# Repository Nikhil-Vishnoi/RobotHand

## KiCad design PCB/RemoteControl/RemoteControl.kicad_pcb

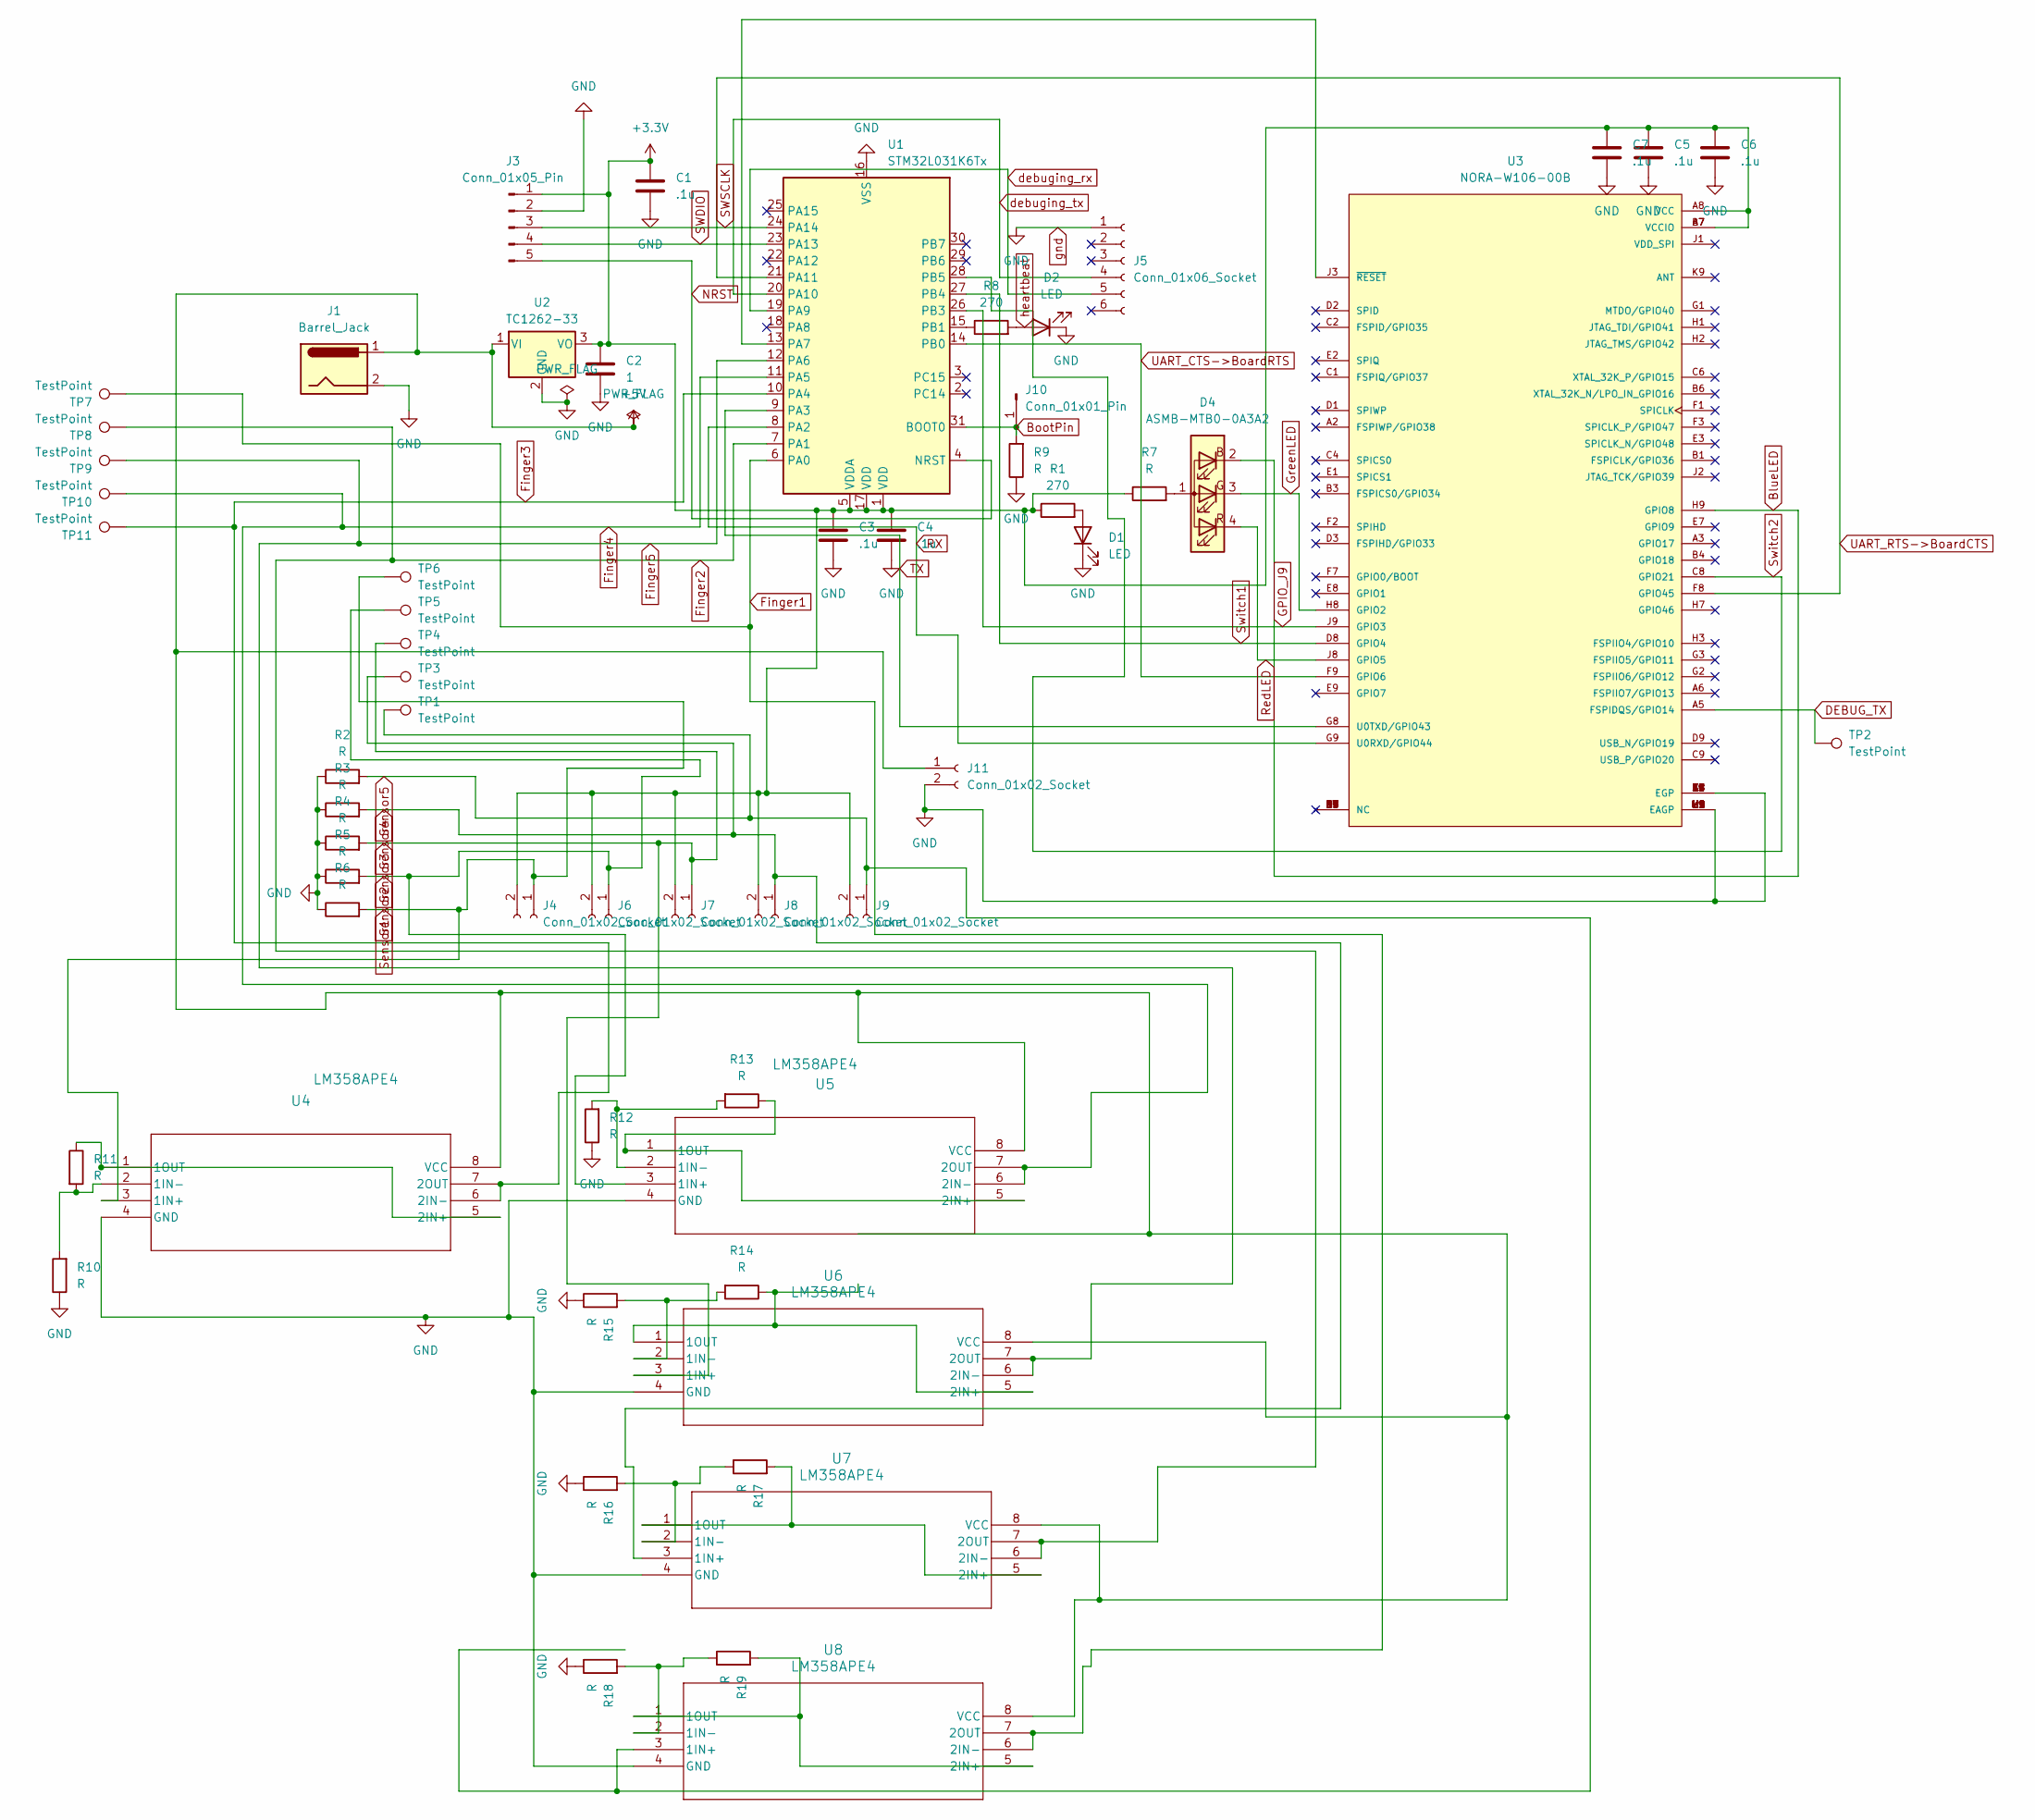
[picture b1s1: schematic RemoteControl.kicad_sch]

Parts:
C1, C3, C4, C5, C6, C7: .1u; C_0805_2012Metric_Pad1.18x1.45mm_HandSolder
C2: 1; C_0805_2012Metric_Pad1.18x1.45mm_HandSolder
D1, D2: LED; LED_1206_3216Metric_Pad1.42x1.75mm_HandSolder
D4: ASMB-MTB0-0A3A2; LED_Avago_PLCC4_3.2x2.8mm_CW
J1: Barrel_Jack; BarrelJack_Wuerth_694106106102_2.0x5.5mm
J3: Conn_01x05_Pin; PinHeader_1x05_P2.54mm_Vertical
J4, J6, J7, J8, J9, J11: Conn_01x02_Socket; PinSocket_1x02_P2.54mm_Horizontal
J5: Conn_01x06_Socket; PinHeader_1x06_P2.54mm_Vertical
J10: Conn_01x01_Pin; PinHeader_1x01_P2.54mm_Vertical
R1, R8: 270; R_0805_2012Metric_Pad1.20x1.40mm_HandSolder
R2, R3, R4, R5, R6, R7, R9, R10, R11, R12, R13, R14, R15, R16, R17, R18, R19: R; R_0805_2012Metric_Pad1.20x1.40mm_HandSolder
TP1, TP2, TP3, TP4, TP5, TP6, TP7, TP8, TP9, TP10, TP11: TestPoint; TestPoint_Pad_2.5x2.5mm
U1: STM32L031K6Tx; LQFP-32_7x7mm_P0.8mm
U2: TC1262-33; SOT-223-3_TabPin2
U3: NORA-W106-00B; XCVR_NORA-W106-00B; PARTREV R03
U4, U5, U6, U7, U8: LM358APE4; P8

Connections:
+3.3V: C1.1, C2.1, C3.1, C4.1, C5.1, C6.1, C7.1, J3.1, J4.2, J6.2, J7.2, J8.2, J9.2, R1.1, R7.1, U1.1 (VDD), U1.5 (VDDA), U1.17 (VDD), U2.3 (VO), U3.A7 (VCCIO), U3.A8 (VCC), U3.B7 (VCCIO)
+5V: J1.1, J11.1, U2.1 (VI), U4.8 (VCC), U5.8 (VCC), U6.8 (VCC), U7.8 (VCC), U8.8 (VCC)
BlueLED: D4.2 (BK), U3.H9 (GPIO8)
BootPin: J10.1, R9.2, U1.31 (BOOT0)
DEBUG_TX: TP2.1, U3.A5 (FSPIDQS/GPIO14)
Finger1: TP7.1, U1.6 (PA0), U8.6 (2IN-), U8.7 (2OUT)
Finger2: TP8.1, U1.7 (PA1), U7.6 (2IN-), U7.7 (2OUT)
Finger3: TP11.1, U1.10 (PA4), U4.6 (2IN-), U4.7 (2OUT)
Finger4: TP10.1, U1.11 (PA5), U5.6 (2IN-), U5.7 (2OUT)
Finger5: TP9.1, U1.12 (PA6), U6.6 (2IN-), U6.7 (2OUT)
GPIO_J9: U1.26 (PB3), U3.J9 (GPIO3)
GreenLED: D4.3 (GK), U3.H8 (GPIO2)
NRST: J3.5, U1.4 (NRST)
unnamed: D1.2 (A), R1.2
unnamed: D2.2 (A), R8.2
unnamed: D4.1 (A), R7.2
unnamed: U1.13 (PA7), U3.J3 (~RESET)
unnamed: R8.1, U1.15 (PB1)
unnamed: R10.2, R11.2, U4.2 (1IN-)
unnamed: R11.1, U4.1 (1OUT), U4.5 (2IN+)
unnamed: R12.2, R13.2, U5.2 (1IN-)
unnamed: R13.1, U5.1 (1OUT), U5.5 (2IN+)
unnamed: R14.2, R15.2, U6.2 (1IN-)
unnamed: R14.1, U6.1 (1OUT), U6.5 (2IN+)
unnamed: R16.2, R17.1, U7.2 (1IN-)
unnamed: R17.2, U7.1 (1OUT), U7.5 (2IN+)
unnamed: R18.2, R19.1, U8.2 (1IN-)
unnamed: R19.2, U8.1 (1OUT), U8.5 (2IN+)
RX: U1.8 (PA2), U3.G9 (U0RXD/GPIO44)
RedLED: D4.4 (RK), U3.J8 (GPIO5)
SWDIO: J3.4, U1.23 (PA13)
SWSCLK: J3.3, U1.24 (PA14)
Sensor1: J4.1, R6.2, TP6.1, U4.3 (1IN+)
Sensor2: J6.1, R5.2, TP5.1, U5.3 (1IN+)
Sensor3: J7.1, R4.2, TP4.1, U6.3 (1IN+)
Sensor4: J8.1, R3.2, TP3.1, U7.3 (1IN+)
Sensor5: J9.1, R2.2, TP1.1, U8.3 (1IN+)
Switch1: U1.27 (PB4), U3.D8 (GPIO4)
Switch2: U1.28 (PB5), U3.C8 (GPIO21)
TX: U1.9 (PA3), U3.G8 (U0TXD/GPIO43)
UART_CTS->BoardRTS: U1.14 (PB0), U3.F9 (GPIO6)
UART_RTS->BoardCTS: U1.21 (PA11), U3.F8 (GPIO45)
debuging_rx: J5.5, U1.19 (PA9)
debuging_tx: J5.4, U1.20 (PA10)
gnd: C1.2, C2.2, C3.2, C4.2, C5.2, C6.2, C7.2, D1.1 (K), D2.1 (K), J1.2, J3.2, J5.1, J11.2, R2.1, R3.1, R4.1, R5.1, R6.1, R9.1, R10.1, R12.1, R15.1, R16.1, R18.1, U1.16 (VSS), U1.32 (VSS), U2.2 (GND), U3.A1 (EGP), U3.A9 (EGP), U3.B2 (EGP), U3.B8 (EGP), U3.E4 (EGP), U3.E5 (EGP), U3.F4 (EGP), U3.F5 (EGP), U3.K2 (EGP), U3.K3 (EGP), U3.K5 (EGP), U3.K7 (EGP), U3.K8 (EGP), U3.L1 (EAGP), U3.L9 (EAGP), U3.M1 (EAGP), U3.M2 (EAGP), U3.M8 (EAGP), U3.M9 (EAGP), U4.4 (GND), U5.4 (GND), U6.4 (GND), U7.4 (GND), U8.4 (GND)

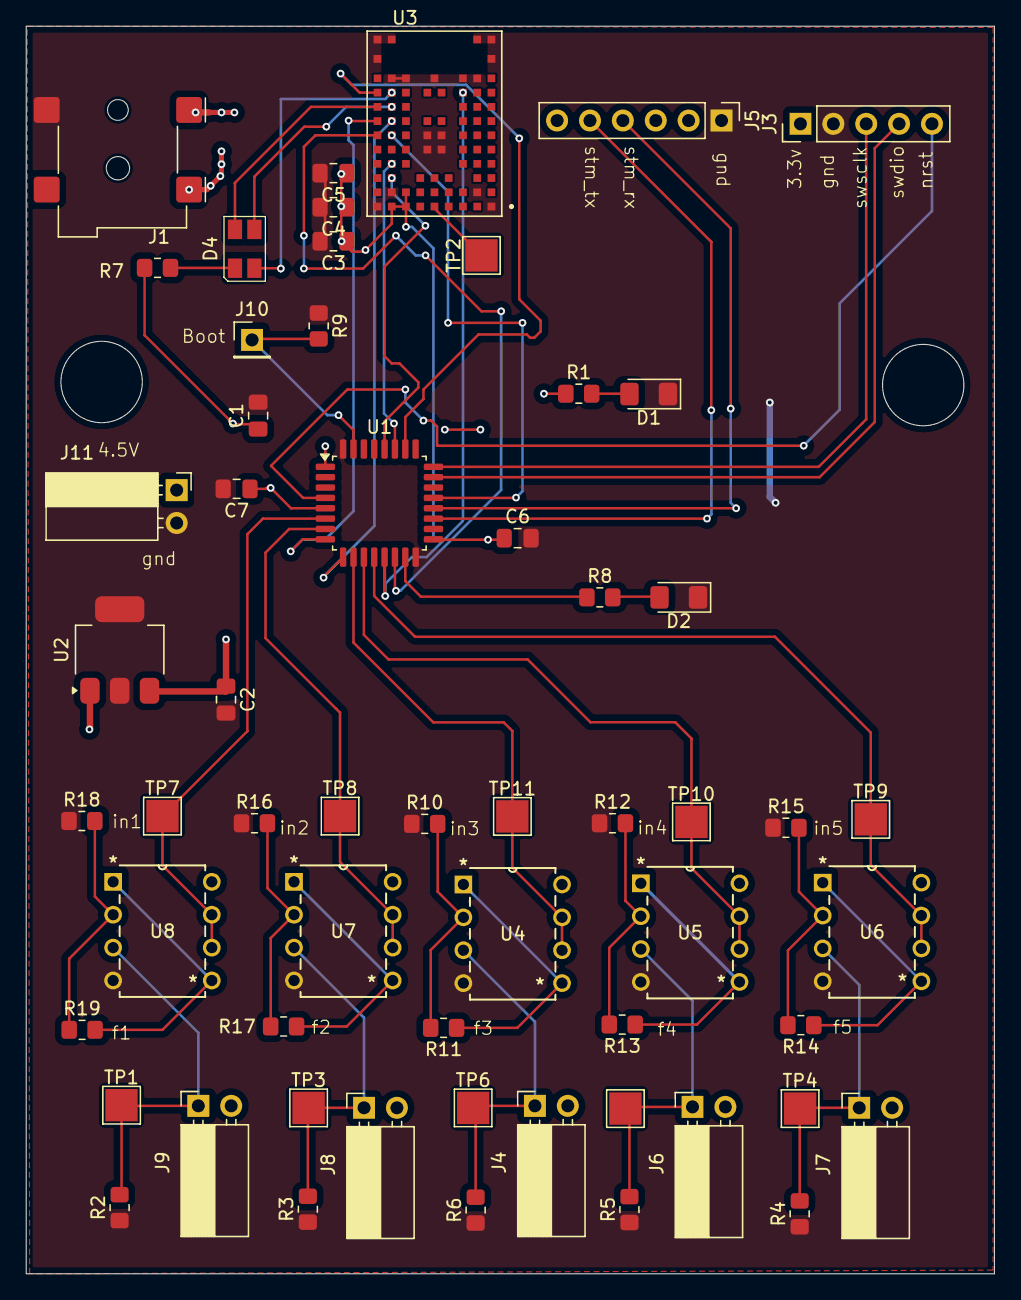
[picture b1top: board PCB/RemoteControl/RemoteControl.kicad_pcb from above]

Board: 2 copper layers, 74.8 x 96.4 mm, 58 parts (0 on the bottom side), 45 nets.

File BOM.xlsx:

Servo Controller
Reference | Qty | Value | DNP | Exclude from BOM | Exclude from Board | Footprint | Datasheet | Digikey Link
C1,C2,C5,C6,C7,C4 | 6.0 | .1u |  |  |  | Capacitor_SMD:C_0504_1310Metric_Pad0.83x1.28mm_HandSolder | ~ | https://www.digikey.com/en/products/detail/passive-plus/0505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
C3 | 1.0 | 1.0 |  |  |  | Capacitor_SMD:C_0504_1310Metric_Pad0.83x1.28mm_HandSolder | ~ | https://www.digikey.com/en/products/detail/murata-electronic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
D1 | 1.0 | ASMB-MTB0-0A3A2 |  |  |  | LED_SMD:LED_Avago_PLCC4_3.2x2.8mm_CW | https://docs.broadcom.com/docs/AV02-4186EN | https://www.mouser.com/ProductDetail/Broadcom-Avago/ASMB-MTB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
D2,D3 | 2.0 | LED |  |  |  | LED_SMD:LED_1206_3216Metric_Pad1.42x1.75mm_HandSolder | ~ | https://www.digikey.com/en/products/detail/everlight-electro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
J1,J2,J3,J4,J7 | 5.0 | Conn_01x03_Pin |  |  |  | Connector_PinHeader_2.54mm:PinHeader_1x03_P2.54mm_Horizontal | ~ | https://www.digikey.com/en/products/detail/w-rth-elektronik/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
J5 | 1.0 | Conn_01x05_Pin |  |  |  | Connector_PinHeader_2.54mm:PinHeader_1x05_P2.54mm_Vertical | ~ | https://www.digikey.com/en/products/detail/te-connectivity-a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
J6 | 1.0 | Conn_01x02_Socket |  |  |  | Connector_PinSocket_2.54mm:PinSocket_1x02_P2.54mm_Horizontal | ~ | https://www.digikey.com/en/products/detail/sullins-connector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
J8 | 1.0 | Barrel_Jack |  |  |  | Connector_BarrelJack:BarrelJack_Wuerth_694106106102_2.0x5.5mm | ~ | https://www.digikey.com/en/products/detail/w-rth-elektronik/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
J9 | 1.0 | Conn_01x06_Socket |  |  |  | Connector_PinSocket_2.54mm:PinSocket_1x06_P2.54mm_Vertical | ~ | https://www.digikey.com/en/products/detail/sullins-connector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
J10 | 1.0 | Conn_01x01_Pin |  |  |  | Connector_PinHeader_2.54mm:PinHeader_1x01_P2.54mm_Vertical | ~ | https://www.digikey.com/en/products/detail/te-connectivity-a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
R1,R3,R4,R2 | 4.0 | 270.0 |  |  |  | Resistor_SMD:R_0805_2012Metric_Pad1.20x1.40mm_HandSolder | ~ | https://www.digikey.com/en/products/detail/panasonic-electro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
TP1,TP2,TP3 | 3.0 | TestPoint |  |  |  | TestPoint:TestPoint_Pad_2.5x2.5mm | ~ | Already on Board
U1 | 1.0 | PCA9685PW |  |  |  | Package_SO:TSSOP-28_4.4x9.7mm_P0.65mm | http://www.nxp.com/docs/en/data-sheet/PCA9685.pdf | Have
U2 | 1.0 | NORA-W106-00B |  |  |  | NORA-W106-00B:XCVR_NORA-W106-00B |  | Have
U3 | 1.0 | TC1262-33 |  |  |  | Package_TO_SOT_SMD:SOT-223-3_TabPin2 | http://ww1.microchip.com/downloads/en/DeviceDoc/21373C.pdf | https://www.digikey.com/en/products/detail/microchip-technol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
U4 | 1.0 | STM32L031K6Tx |  |  |  | Package_QFP:LQFP-32_7x7mm_P0.8mm | https://www.st.com/resource/en/datasheet/stm32l031k6.pdf | Get from supply closet
Servo | 5.0 |  |  |  |  |  |  | https://www.digikey.com/en/products/detail/hitec-commercial-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
Remort Controller
Reference | Qty | Value | DNP | Exclude from BOM | Exclude from Board | Footprint | Datasheet | Digikey Buy Link
C1,C3,C4,C5,C6,C7 | 6.0 | .1u |  |  |  | Capacitor_SMD:C_0504_1310Metric_Pad0.83x1.28mm_HandSolder | ~ | https://www.mouser.com/ProductDetail/Samsung-Electro-Mechani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
C2 | 1.0 | 1.0 |  |  |  | Capacitor_SMD:C_0504_1310Metric_Pad0.83x1.28mm_HandSolder | ~ | https://www.digikey.com/en/products/detail/murata-electronic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
D1,D2 | 2.0 | LED |  |  |  | LED_SMD:LED_1206_3216Metric_Pad1.42x1.75mm_HandSolder | ~ | https://www.digikey.com/en/products/detail/everlight-electro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
D4 | 1.0 | ASMB-MTB0-0A3A2 |  |  |  | LED_SMD:LED_Avago_PLCC4_3.2x2.8mm_CW | https://docs.broadcom.com/docs/AV02-4186EN | https://www.mouser.com/ProductDetail/Broadcom-Avago/ASMB-MTB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
J1 | 1.0 | Barrel_Jack |  |  |  | Connector_BarrelJack:BarrelJack_Wuerth_694106106102_2.0x5.5mm | ~ | https://www.digikey.com/en/products/detail/w-rth-elektronik/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
J3 | 1.0 | Conn_01x05_Pin |  |  |  | Connector_PinHeader_2.54mm:PinHeader_1x05_P2.54mm_Vertical | ~ | https://www.digikey.com/en/products/detail/te-connectivity-a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
J4,J6,J7,J8,J9,J11 | 6.0 | Conn_01x02_Socket |  |  |  | Connector_PinSocket_2.54mm:PinSocket_1x02_P2.54mm_Horizontal | ~ | https://www.digikey.com/en/products/detail/sullins-connector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
J5 | 1.0 | Conn_01x06_Socket |  |  |  | Connector_PinHeader_2.54mm:PinHeader_1x06_P2.54mm_Vertical | ~ | https://www.digikey.com/en/products/detail/sullins-connector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
J10 | 1.0 | Conn_01x01_Pin |  |  |  | Connector_PinHeader_2.54mm:PinHeader_1x01_P2.54mm_Vertical | ~ | https://www.digikey.com/en/products/detail/te-connectivity-a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
R1,R8,R9,R7 | 2.0 | 270.0 |  |  |  | Resistor_SMD:R_0805_2012Metric_Pad1.20x1.40mm_HandSolder | ~ | https://www.digikey.com/en/products/detail/panasonic-electro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
R2,R3,R4,R5,R6 | 5.0 | 200k |  |  |  | Resistor_SMD:R_0805_2012Metric_Pad1.20x1.40mm_HandSolder | ~ | https://www.digikey.com/en/products/detail/yageo/RC0805JR-07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
R11,R13,R14,R17,R19 | 5.0 | 10k |  |  |  | Resistor_SMD:R_0805_2012Metric_Pad1.20x1.40mm_HandSolder | ~ | https://www.digikey.com/en/products/detail/yageo/RC0805FR-07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
R10,R12,R15,R16,R18 | 17.0 | 5k |  |  |  | Resistor_SMD:R_0805_2012Metric_Pad1.20x1.40mm_HandSolder | ~ | https://www.digikey.com/en/products/detail/vishay-dale/CRCW0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
TP1,TP2,TP3,TP4,TP5,TP6,TP7,TP8,TP9,TP10,TP11 | 11.0 | TestPoint |  |  |  | TestPoint:TestPoint_Pad_2.5x2.5mm | ~ | Already on Board
U1 | 1.0 | STM32L031K6Tx |  |  |  | Package_QFP:LQFP-32_7x7mm_P0.8mm | https://www.st.com/resource/en/datasheet/stm32l031k6.pdf | Get from the supply closet
U2 | 1.0 | TC1262-33 |  |  |  | Package_TO_SOT_SMD:SOT-223-3_TabPin2 | http://ww1.microchip.com/downloads/en/DeviceDoc/21373C.pdf | https://www.digikey.com/en/products/detail/microchip-technol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
U3 | 1.0 | NORA-W106-00B |  |  |  | NORA-W106-00B:XCVR_NORA-W106-00B |  | Have
U4,U5,U6,U7,U8 | 5.0 | LM358APE4 |  |  |  | lm358:P8 | https://www.ti.com/lit/gpn/lm358 | https://www.digikey.com/en/products/detail/texas-instruments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
 | 5.0

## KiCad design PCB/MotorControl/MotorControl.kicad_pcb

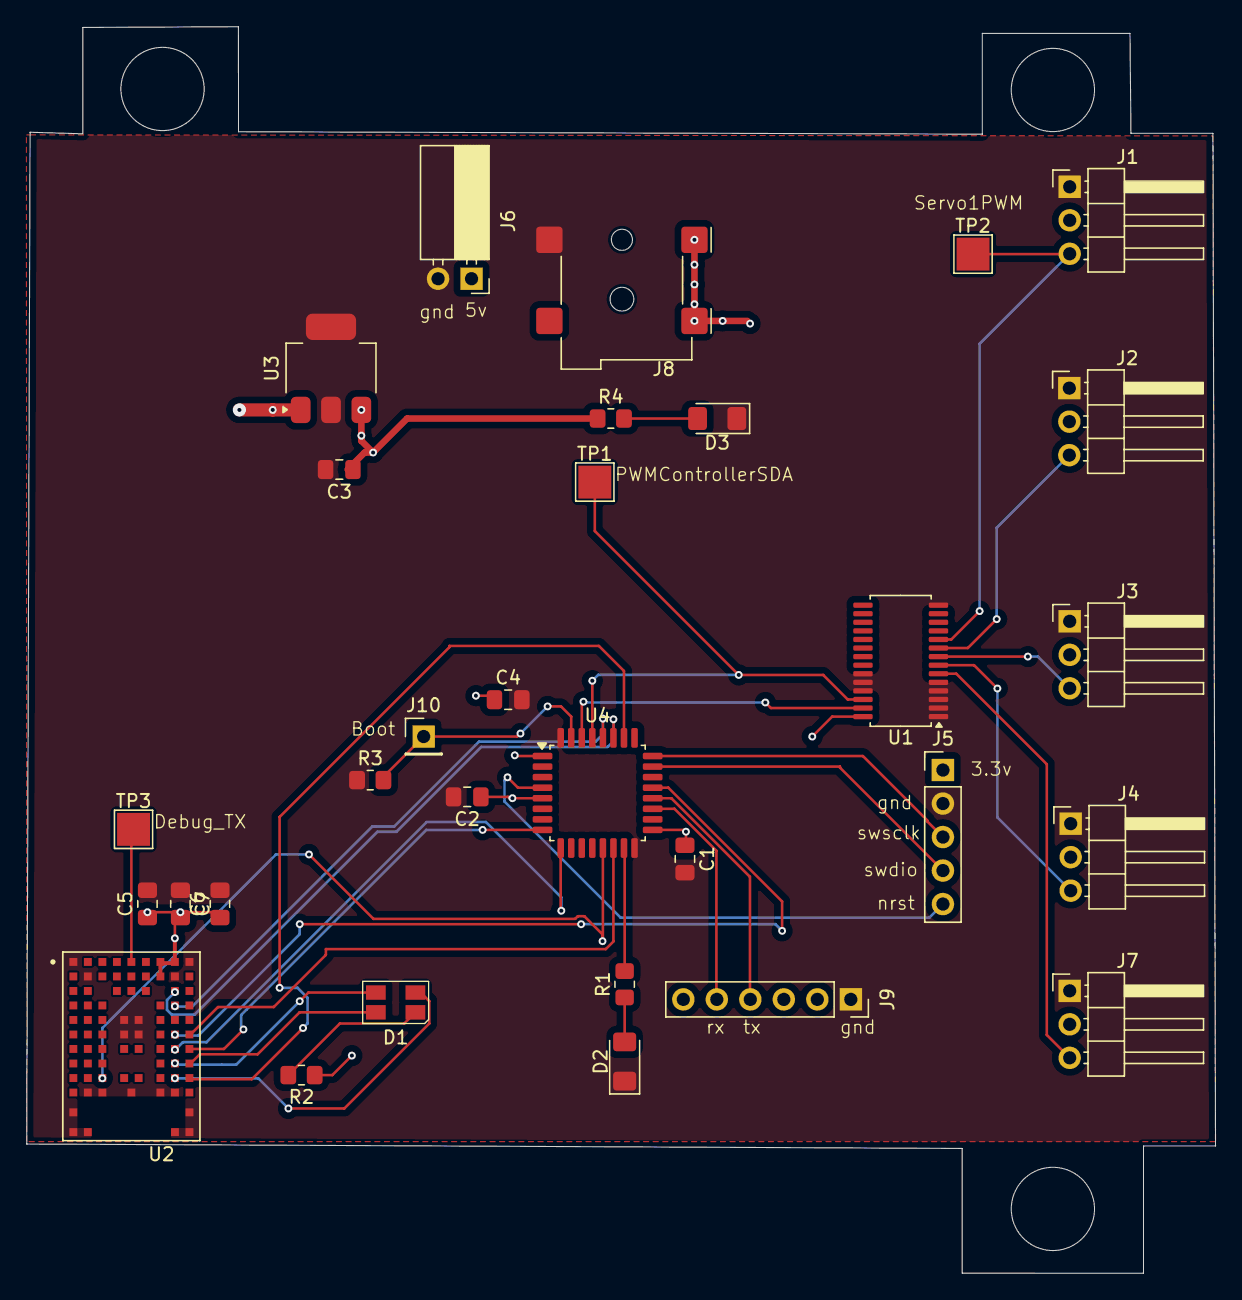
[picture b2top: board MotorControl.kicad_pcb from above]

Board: 2 copper layers, 90.1 x 94.5 mm, 31 parts (0 on the bottom side), 32 nets.

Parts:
C1, C2, C5, C6, C7: C; C_0805_2012Metric_Pad1.18x1.45mm_HandSolder
C3: 1; C_0805_2012Metric_Pad1.18x1.45mm_HandSolder
C4: .1u; C_0805_2012Metric_Pad1.18x1.45mm_HandSolder
D1: ASMB-MTB0-0A3A2; LED_Avago_PLCC4_3.2x2.8mm_CW
D2, D3: LED; LED_1206_3216Metric_Pad1.42x1.75mm_HandSolder
J1, J2, J3, J4, J7: Conn_01x03_Pin; PinHeader_1x03_P2.54mm_Horizontal
J5: Conn_01x05_Pin; PinHeader_1x05_P2.54mm_Vertical
J6: Conn_01x02_Socket; PinSocket_1x02_P2.54mm_Horizontal
J8: Barrel_Jack; BarrelJack_Wuerth_694106106102_2.0x5.5mm
J9: Conn_01x06_Socket; PinSocket_1x06_P2.54mm_Vertical
J10: Conn_01x01_Pin; PinHeader_1x01_P2.54mm_Vertical
R1, R3, R4: 270; R_0805_2012Metric_Pad1.20x1.40mm_HandSolder
R2: R; R_0805_2012Metric_Pad1.20x1.40mm_HandSolder
TP1, TP2, TP3: TestPoint; TestPoint_Pad_2.5x2.5mm
U1: PCA9685PW; TSSOP-28_4.4x9.7mm_P0.65mm
U2: NORA-W106-00B; XCVR_NORA-W106-00B
U3: TC1262-33; SOT-223-3_TabPin2
U4: STM32L031K6Tx; LQFP-32_7x7mm_P0.8mm

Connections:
5V: J1.2, J2.2, J3.2, J4.2, J6.1, J7.2, J8.1, U3.1 (VI)
+3.3V: C1.1, C2.1, C3.1, C4.1, C5.1, C6.1, C7.2, J5.1, R2.1, R4.1, U1.28 (VDD), U2.A7 (VCCIO), U2.A8 (VCC), U2.B7 (VCCIO), U3.3 (VO), U4.1 (VDD), U4.5 (VDDA), U4.17 (VDD)
BlueLED: D1.2 (BK), U2.H9 (GPIO8)
Boot: J10.1, R3.2, U4.31 (BOOT0)
DebugTX: TP3.1, U2.A5 (FSPIDQS/GPIO14)
Debug_rx: J9.5, U4.19 (PA9)
Debug_tx: J9.4, U4.20 (PA10)
GND: C1.2, C2.2, C3.2, C4.2, C5.2, C6.2, C7.1, D2.1 (K), D3.1 (K), J1.1, J2.1, J3.1, J4.1, J5.2, J6.2, J7.1, J8.2, J9.1, R3.1, U1.1 (A0), U1.2 (A1), U1.3 (A2), U1.4 (A3), U1.5 (A4), U1.14 (VSS), U1.23 (~OE), U1.24 (A5), U1.25 (EXTCLK), U2.A1 (EGP), U2.A9 (EGP), U2.B2 (EGP), U2.B8 (EGP), U2.E4 (EGP), U2.E5 (EGP), U2.F4 (EGP), U2.F5 (EGP), U2.K2 (EGP), U2.K3 (EGP), U2.K5 (EGP), U2.K7 (EGP), U2.K8 (EGP), U2.L1 (EAGP), U2.L9 (EAGP), U2.M1 (EAGP), U2.M2 (EAGP), U2.M8 (EAGP), U2.M9 (EAGP), U3.2 (GND), U4.16 (VSS), U4.32 (VSS)
GPIO_J9: U2.J9 (GPIO3), U4.26 (PB3)
GreenLED: D1.3 (GK), U2.H8 (GPIO2)
HeartBeat: R1.2, U4.15 (PB1)
Motor1PWM: J1.3, TP2.1, U1.10 (LED4)
MotorControl_SCL: TP1.1, U1.26 (SCL), U4.29 (PB6)
NRST: J5.5, U4.4 (NRST)
unnamed: D1.1 (A), R2.2
unnamed: D2.2 (A), R1.1
unnamed: D3.2 (A), R4.2
unnamed: J2.3, U1.9 (LED3)
unnamed: J3.3, U1.8 (LED2)
unnamed: J4.3, U1.7 (LED1)
unnamed: J7.3, U1.6 (LED0)
unnamed: U1.27 (SDA), U4.30 (PB7)
unnamed: U2.J3 (~RESET), U4.13 (PA7)
RX: U2.G8 (U0TXD/GPIO43), U4.9 (PA3)
RedLED: D1.4 (RK), U2.J8 (GPIO5)
SWDIO: J5.4, U4.23 (PA13)
SWSCLK: J5.3, U4.24 (PA14)
Switch1: U2.D8 (GPIO4), U4.28 (PB5)
Switch2: U2.C8 (GPIO21), U4.27 (PB4)
TX: U2.G9 (U0RXD/GPIO44), U4.8 (PA2)
UART_CTS->Board_RTS: U2.F9 (GPIO6), U4.14 (PB0)
UART_RTS->Board_CTS: U2.F8 (GPIO45), U4.21 (PA11)

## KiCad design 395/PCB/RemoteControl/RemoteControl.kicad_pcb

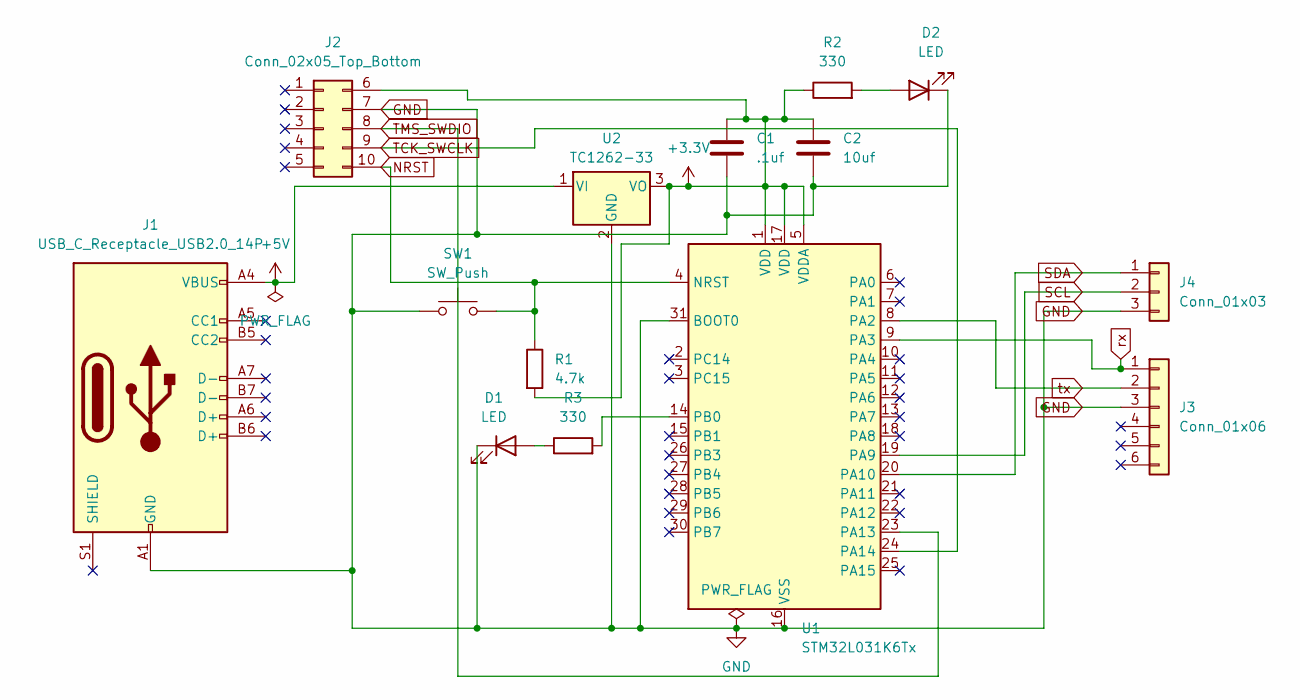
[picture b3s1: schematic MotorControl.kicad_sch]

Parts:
C1: .1uf; C_0805_2012Metric_Pad1.18x1.45mm_HandSolder
C2: 10uf; C_0805_2012Metric_Pad1.18x1.45mm_HandSolder
D1, D2: LED; LED_0805_2012Metric_Pad1.15x1.40mm_HandSolder
J1: USB_C_Receptacle_USB2.0_14P; USB_C_Receptacle_GCT_USB4085
J2: Conn_02x05_Top_Bottom; PinHeader_2x05_P2.54mm_Vertical
J3: Conn_01x06; PinHeader_1x06_P2.54mm_Vertical
J4: Conn_01x03; PinHeader_1x03_P2.54mm_Vertical
R1: 4.7k; R_0805_2012Metric_Pad1.20x1.40mm_HandSolder
R2, R3: 330; R_0805_2012Metric_Pad1.20x1.40mm_HandSolder
SW1: SW_Push; SW_PUSH_6mm_H4.3mm
U1: STM32L031K6Tx; LQFP-32_7x7mm_P0.8mm
U2: TC1262-33; SOT-223-3_TabPin2

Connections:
+5V: J1.A4 (VBUS), J1.A9 (VBUS), J1.B4 (VBUS), J1.B9 (VBUS), U2.1 (VI)
GND: C1.2, C2.2, D1.1 (K), D2.1 (K), J1.A1 (GND), J1.A12 (GND), J1.B1 (GND), J1.B12 (GND), J2.7, J3.3, J4.3, SW1.1, U1.16 (VSS), U1.31 (BOOT0), U1.32 (VSS), U2.2 (GND)
NRST: J2.10, R1.1, SW1.2, U1.4 (NRST)
unnamed: D1.2 (A), R3.1
unnamed: D2.2 (A), R2.2
unnamed: R3.2, U1.14 (PB0)
SCL: J4.2, U1.19 (PA9)
SDA: J4.1, U1.20 (PA10)
TCK_SWCLK: J2.9, U1.24 (PA14)
TMS_SWDIO: J2.8, U1.23 (PA13)
VAPP: C1.1, C2.1, J2.6, R1.2, R2.1, U1.1 (VDD), U1.5 (VDDA), U1.17 (VDD), U2.3 (VO)
rx: J3.1, U1.9 (PA3)
tx: J3.2, U1.8 (PA2)

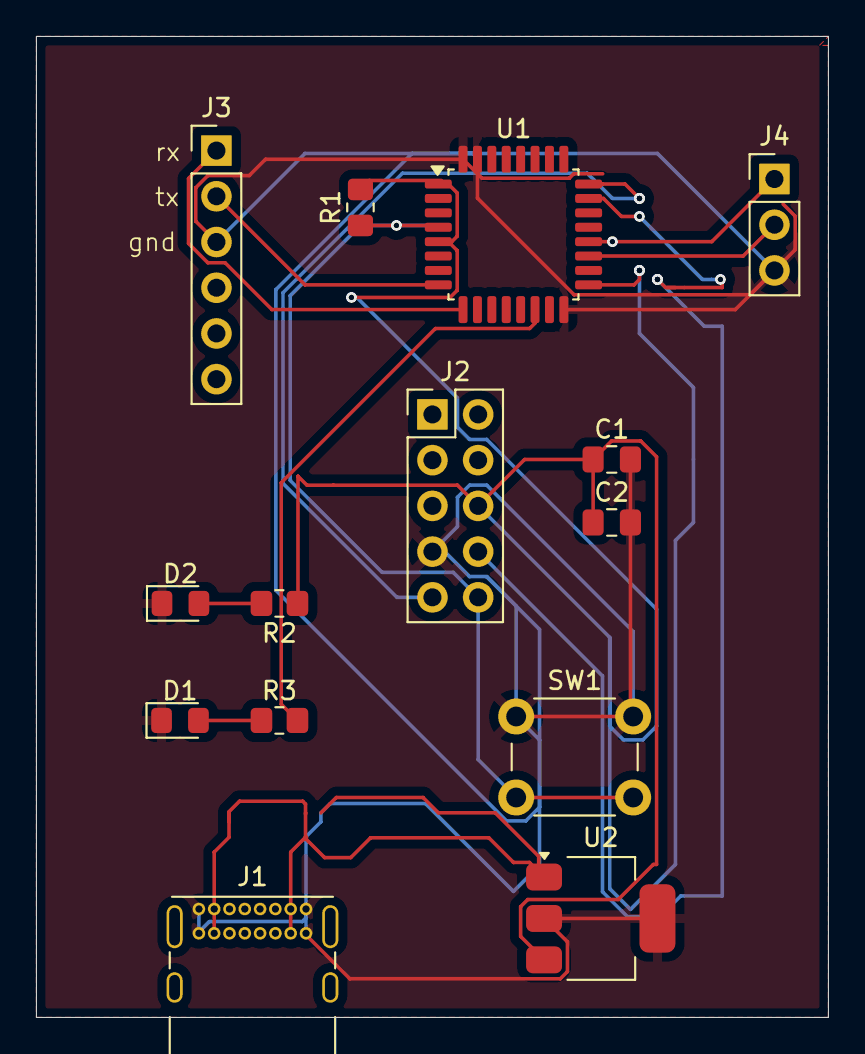
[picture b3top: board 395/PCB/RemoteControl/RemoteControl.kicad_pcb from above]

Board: 2 copper layers, 44.0 x 54.5 mm, 14 parts (0 on the bottom side), 13 nets.

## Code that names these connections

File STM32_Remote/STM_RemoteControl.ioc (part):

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Mcu.Name=STM32L031K(4-6)Tx
Mcu.Package=LQFP32
Mcu.UserName=STM32L031K6Tx
PA0-CK_IN.Mode=IN0
PA0-CK_IN.Signal=ADC_IN0
PA1.Mode=IN1
PA1.Signal=ADC_IN1
PA10.Mode=Asynchronous
PA10.Signal=USART2_RX
PA13.Mode=Serial_Wire
PA13.Signal=SYS_SWDIO
PA14.Mode=Serial_Wire
PA14.Signal=SYS_SWCLK
PA2.Mode=Asynchronous
PA2.Signal=LPUART1_TX
PA3.Mode=Asynchronous
PA3.Signal=LPUART1_RX
PA4.Mode=IN4
PA4.Signal=ADC_IN4
PA5.Mode=IN5
PA5.Signal=ADC_IN5
PA6.Mode=IN6
PA6.Signal=ADC_IN6
PA7.GPIOParameters=GPIO_Label
PA7.GPIO_Label=NReset
PA7.Signal=GPIO_Output
PA9.Mode=Asynchronous
PA9.Signal=USART2_TX
PB1.GPIOParameters=GPIO_Label
PB1.GPIO_Label=LED
PB1.Signal=GPIO_Output
PB3.GPIOParameters=GPIO_Label
PB3.GPIO_Label=GPIO_J9
PB3.Signal=GPIO_Output
PB4.GPIOParameters=GPIO_Label
PB4.GPIO_Label=Switch1
PB4.Signal=GPIO_Output
PB5.GPIOParameters=GPIO_Label
PB5.GPIO_Label=Switch2
PB5.Signal=GPIO_Output
RCC.HSE_VALUE=8000000
RCC.SYSCLKFreq_VALUE=2097000
board=custom

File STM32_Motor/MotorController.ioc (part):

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Mcu.Name=STM32L031K(4-6)Tx
Mcu.Package=LQFP32
Mcu.UserName=STM32L031K6Tx
PA10.GPIOParameters=GPIO_PuPd
PA10.GPIO_PuPd=GPIO_PULLUP
PA10.Mode=Asynchronous
PA10.Signal=USART2_RX
PA13.Mode=Serial_Wire
PA13.Signal=SYS_SWDIO
PA14.Mode=Serial_Wire
PA14.Signal=SYS_SWCLK
PA2.Mode=Asynchronous
PA2.Signal=LPUART1_TX
PA3.Mode=Asynchronous
PA3.Signal=LPUART1_RX
PA7.GPIOParameters=PinState,GPIO_PuPd,GPIO_Label,GPIO_ModeDefaultOutputPP
PA7.GPIO_Label=NReset
PA7.GPIO_ModeDefaultOutputPP=GPIO_MODE_OUTPUT_PP
PA7.GPIO_PuPd=GPIO_NOPULL
PA7.PinState=GPIO_PIN_RESET
PA7.Signal=GPIO_Output
PA9.GPIOParameters=GPIO_PuPd
PA9.GPIO_PuPd=GPIO_PULLUP
PA9.Mode=Asynchronous
PA9.Signal=USART2_TX
PB1.GPIOParameters=GPIO_Label
PB1.GPIO_Label=LED
PB1.Signal=GPIO_Output
PB3.GPIOParameters=PinState,GPIO_Label
PB3.GPIO_Label=GPIO_J9
PB3.PinState=GPIO_PIN_RESET
PB3.Signal=GPIO_Output
PB4.GPIOParameters=GPIO_Speed,PinState,GPIO_PuPd,GPIO_Label,GPIO_ModeDefaultOutputPP
PB4.GPIO_Label=Switch1
PB4.GPIO_ModeDefaultOutputPP=GPIO_MODE_OUTPUT_OD
PB4.GPIO_PuPd=GPIO_NOPULL
PB4.GPIO_Speed=GPIO_SPEED_FREQ_VERY_HIGH
PB4.PinState=GPIO_PIN_RESET
PB4.Signal=GPIO_Output
PB5.GPIOParameters=GPIO_Speed,PinState,GPIO_PuPd,GPIO_Label,GPIO_ModeDefaultOutputPP
PB5.GPIO_Label=Switch2
PB5.GPIO_ModeDefaultOutputPP=GPIO_MODE_OUTPUT_OD
PB5.GPIO_PuPd=GPIO_NOPULL
PB5.GPIO_Speed=GPIO_SPEED_FREQ_VERY_HIGH
PB5.PinState=GPIO_PIN_RESET
PB5.Signal=GPIO_Output
PB6.GPIOParameters=GPIO_Pu
PB6.GPIO_Pu=GPIO_PULLUP
PB6.Mode=I2C
PB6.Signal=I2C1_SCL
PB7.GPIOParameters=GPIO_Pu
PB7.GPIO_Pu=GPIO_PULLUP
PB7.Mode=I2C
PB7.Signal=I2C1_SDA
RCC.HSE_VALUE=8000000
RCC.SYSCLKFreq_VALUE=2097000
board=custom

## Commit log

2025-09-17 push
2025-09-20 wasd
2025-09-21 Routing for motor control PCB
2025-09-22 Passing DRC
2025-10-01 Pushing
2025-10-01 Motor Control
2025-10-01 Stuff
2025-10-06 Added stm code
2025-10-07 Pushing updated servo controller
2025-10-08 Remote Control
2025-10-08 Motor
2025-10-10 Updated remote control
2025-10-10 Thing
2025-10-10 mwasd
2025-10-10 Updated Motor Control
2025-10-10 Boom
2025-10-17 final boards
2025-10-26 pushing workspace
2025-11-30 Remote Control Code
2025-12-01 start of Nora util functions
2025-12-05 saving workspace
2025-12-15 added cad files
